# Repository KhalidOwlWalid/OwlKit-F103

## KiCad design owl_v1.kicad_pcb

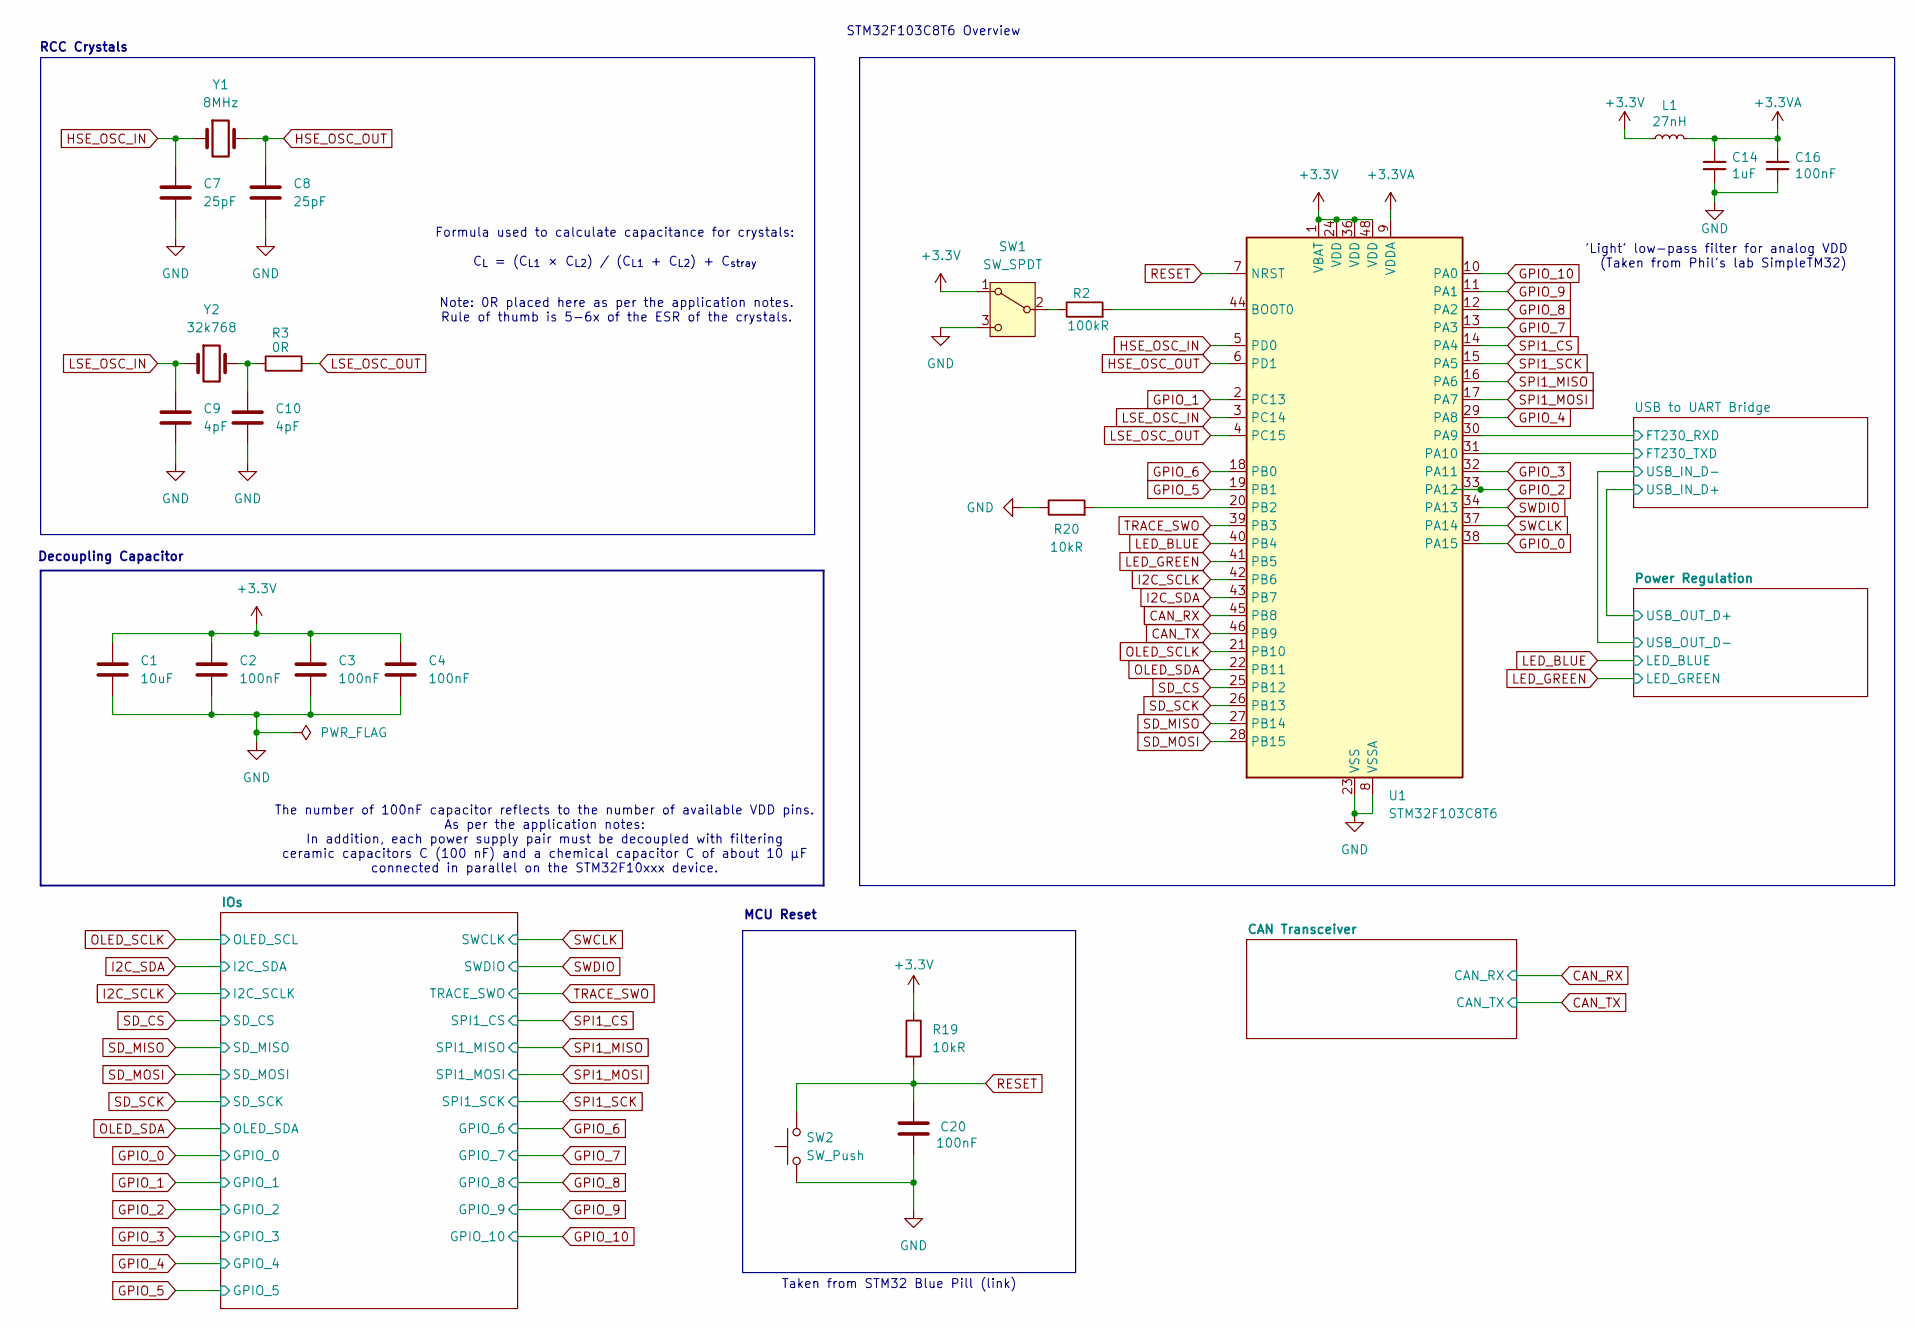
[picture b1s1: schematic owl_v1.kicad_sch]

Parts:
C1: 10uF; C_0603_1608Metric
C2, C3, C4, C20: 100nF; C_0603_1608Metric
C7, C8: 25pF; C_0603_1608Metric
C9, C10: 4pF; C_0603_1608Metric
C14: 1uF; C_0603_1608Metric; LCSC Part # C52923
C16: 100nF; C_0603_1608Metric; LCSC Part # C1525
L1: 27nH; L_0603_1608Metric; LCSC Part # C18830
R2: 100kR; R_0603_1608Metric
R3: 0R; R_0603_1608Metric
R19, R20: 10kR; R_0603_1608Metric
SW1: SW_SPDT; SW_SPDT_CK_JS102011SAQN
SW2: SW_Push; SW_PUSH_6mm
U1: STM32F103C8T6; LQFP-48_7x7mm_P0.5mm
Y1: 8MHz; Crystal_SMD_HC49-SD
Y2: 32k768; Crystal_SMD_MicroCrystal_CC8V-T1A-2Pin_2.0x1.2mm_HandSolder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

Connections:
+3.3V: C1.1, C2.1, C3.1, C4.1, L1.1, R19.1, SW1.1 (A), U1.1 (VBAT), U1.24 (VDD), U1.36 (VDD), U1.48 (VDD); also elsewhere on the board
+3.3VA: C14.1, C16.1, L1.2, U1.9 (VDDA)
/owl_v1/USB to UART Bridge/FT230_RXD: U1.30 (PA9); also elsewhere on the board
/owl_v1/USB to UART Bridge/FT230_TXD: U1.31 (PA10); also elsewhere on the board
CAN_RX: U1.45 (PB8); also elsewhere on the board
CAN_TX: U1.46 (PB9); also elsewhere on the board
GND: C1.2, C2.2, C3.2, C4.2, C7.2, C8.2, C9.2, C10.2, C14.2, C16.2, C20.1, R20.1, SW1.3 (C), SW2.1, U1.8 (VSSA), U1.23 (VSS), U1.35 (VSS), U1.47 (VSS); also elsewhere on the board
GPIO_0: U1.38 (PA15); also elsewhere on the board
GPIO_1: U1.2 (PC13); also elsewhere on the board
GPIO_2: U1.33 (PA12); also elsewhere on the board
GPIO_3: U1.32 (PA11); also elsewhere on the board
GPIO_4: U1.29 (PA8); also elsewhere on the board
GPIO_5: U1.19 (PB1); also elsewhere on the board
GPIO_6: U1.18 (PB0); also elsewhere on the board
GPIO_7: U1.13 (PA3); also elsewhere on the board
GPIO_8: U1.12 (PA2); also elsewhere on the board
GPIO_9: U1.11 (PA1); also elsewhere on the board
GPIO_10: U1.10 (PA0); also elsewhere on the board
HSE_OSC_IN: C7.1, U1.5 (PD0), Y1.1
HSE_OSC_OUT: C8.1, U1.6 (PD1), Y1.2
I2C_SCLK: U1.42 (PB6); also elsewhere on the board
I2C_SDA: U1.43 (PB7); also elsewhere on the board
LED_BLUE: U1.40 (PB4); also elsewhere on the board
LED_GREEN: U1.41 (PB5); also elsewhere on the board
LSE_OSC_IN: C9.1, U1.3 (PC14), Y2.1
LSE_OSC_OUT: R3.2, U1.4 (PC15)
unnamed: C10.1, R3.1, Y2.2
unnamed: R2.1, SW1.2 (B)
unnamed: R2.2, U1.44 (BOOT0)
unnamed: R20.2, U1.20 (PB2)
OLED_SCLK: U1.21 (PB10); also elsewhere on the board
OLED_SDA: U1.22 (PB11); also elsewhere on the board
RESET: C20.2, R19.2, SW2.2, U1.7 (NRST)
SD_CS: U1.25 (PB12); also elsewhere on the board
SD_MISO: U1.27 (PB14); also elsewhere on the board
SD_MOSI: U1.28 (PB15); also elsewhere on the board
SD_SCK: U1.26 (PB13); also elsewhere on the board
SPI1_CS: U1.14 (PA4); also elsewhere on the board
SPI1_MISO: U1.16 (PA6); also elsewhere on the board
SPI1_MOSI: U1.17 (PA7); also elsewhere on the board
SPI1_SCK: U1.15 (PA5); also elsewhere on the board
SWCLK: U1.37 (PA14); also elsewhere on the board
SWDIO: U1.34 (PA13); also elsewhere on the board
TRACE_SWO: U1.39 (PB3); also elsewhere on the board

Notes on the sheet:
MCU Reset
Formula used to calculate capacitance for crystals: C_{L} = (C_{L1} × C_{L2}) / (C_{L1} + C_{L2}) + C_{stray}
RCC Crystals
STM32F103C8T6 Overview
The number of 100nF capacitor reflects to the number of available VDD pins. As per the application notes: In addition, each power supply pair must be decoupled with filtering ceramic capacitors C (100 nF) and a chemical capacitor C of about 10 μF connected in parallel on the STM32F10xxx device.
Decoupling Capacitor
Taken from STM32 Blue Pill (link)
Note: 0R placed here as per the application notes. Rule of thumb is 5-6x of the ESR of the crystals.
'Light' low-pass filter for analog VDD (Taken from Phil's lab SimpleTM32)

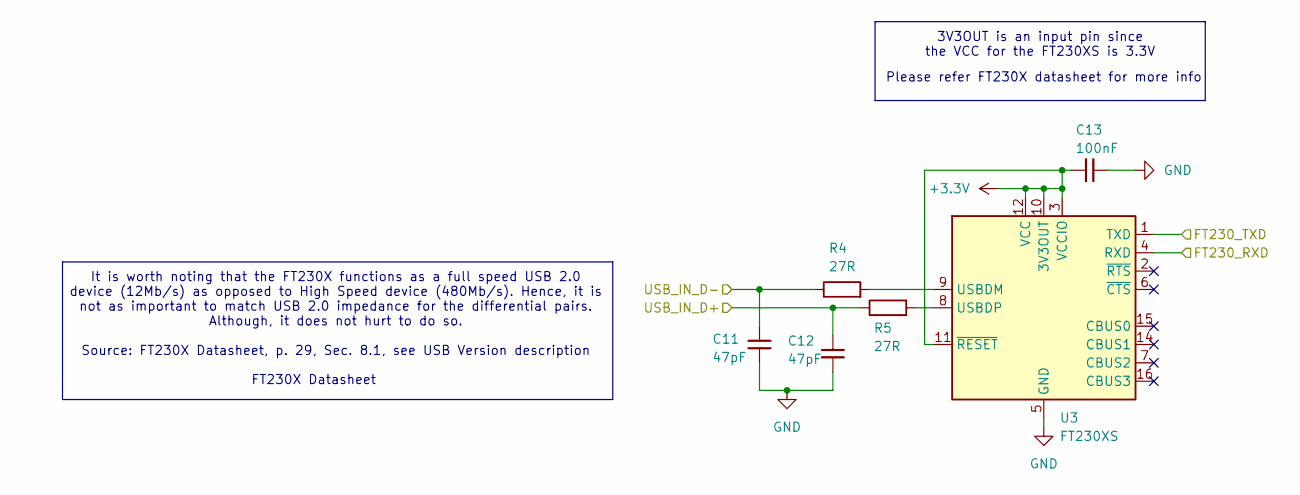
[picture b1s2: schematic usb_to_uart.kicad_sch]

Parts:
C11, C12: 47pF; C_0603_1608Metric
C13: 100nF; C_0603_1608Metric
R4, R5: 27R; R_0603_1608Metric
U3: FT230XS; SSOP-16_3.9x4.9mm_P0.635mm

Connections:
+3.3V: C13.2, U3.3 (VCCIO), U3.10 (3V3OUT), U3.11 (~RESET), U3.12 (VCC); also elsewhere on the board
/owl_v1/Power Regulation/USB_OUT_D+: C12.1, R5.1; also elsewhere on the board
/owl_v1/Power Regulation/USB_OUT_D-: C11.1, R4.1; also elsewhere on the board
/owl_v1/USB to UART Bridge/FT230_RXD: U3.4 (RXD); also elsewhere on the board
/owl_v1/USB to UART Bridge/FT230_TXD: U3.1 (TXD); also elsewhere on the board
GND: C11.2, C12.2, C13.1, U3.5 (GND), U3.13 (GND); also elsewhere on the board
unnamed: R4.2, U3.9 (USBDM)
unnamed: R5.2, U3.8 (USBDP)

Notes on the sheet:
Please refer FT230X datasheet for more info
3V3OUT is an input pin since the VCC for the FT230XS is 3.3V
FT230X Datasheet
It is worth noting that the FT230X functions as a full speed USB 2.0 device (12Mb/s) as opposed to High Speed device (480Mb/s). Hence, it is not as important to match USB 2.0 impedance for the differential pairs. Although, it does not hurt to do so. Source: FT230X Datasheet, p. 29, Sec. 8.1, see US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

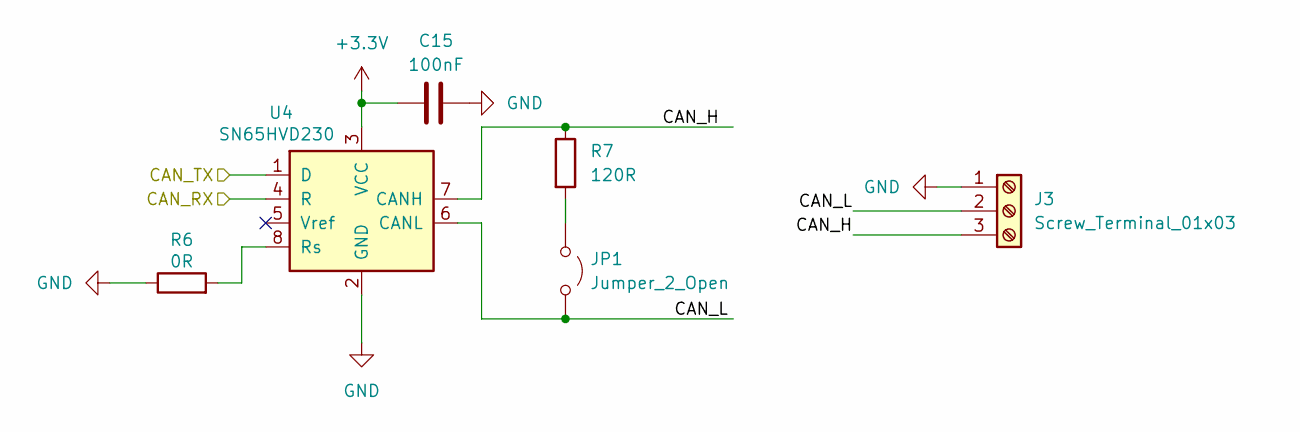
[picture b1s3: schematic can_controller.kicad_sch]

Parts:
C15: 100nF; C_0603_1608Metric
J3: Screw_Terminal_01x03; TerminalBlock_Phoenix_PT-1,5-3-3.5-H_1x03_P3.50mm_Horizontal
JP1: Jumper_2_Open; PinHeader_1x02_P2.54mm_Vertical
R6: 0R; R_0603_1608Metric
R7: 120R; R_0603_1608Metric
U4: SN65HVD230; SOIC-8_3.9x4.9mm_P1.27mm

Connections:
+3.3V: C15.1, U4.3 (VCC); also elsewhere on the board
/owl_v1/CAN Transceiver/CAN_H: J3.3, R7.1, U4.7 (CANH)
/owl_v1/CAN Transceiver/CAN_L: J3.2, JP1.2 (B), U4.6 (CANL)
CAN_RX: U4.4 (R); also elsewhere on the board
CAN_TX: U4.1 (D); also elsewhere on the board
GND: C15.2, J3.1, R6.1, U4.2 (GND); also elsewhere on the board
unnamed: JP1.1 (A), R7.2
unnamed: R6.2, U4.8 (Rs)

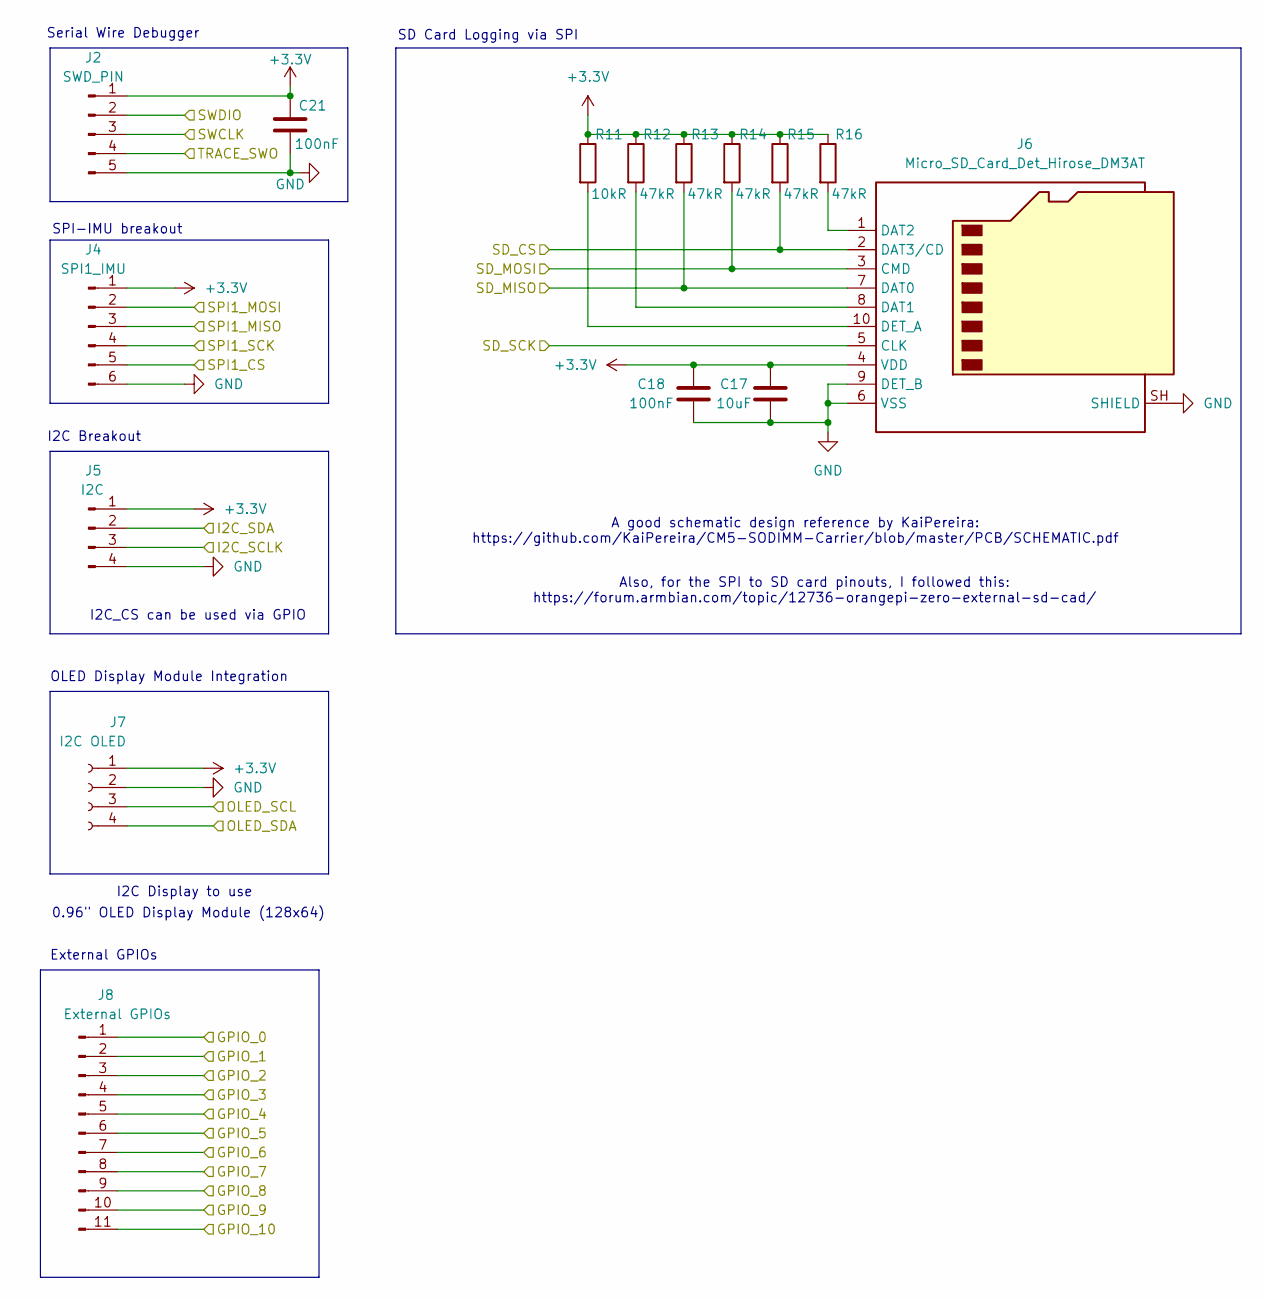
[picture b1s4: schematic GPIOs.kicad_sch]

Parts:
C17: 10uF; C_0603_1608Metric
C18, C21: 100nF; C_0603_1608Metric
J2: SWD_PIN; PinHeader_1x05_P2.54mm_Vertical
J4: SPI1_IMU; PinHeader_1x06_P2.54mm_Vertical
J5: I2C; PinHeader_1x04_P2.54mm_Vertical
J6: Micro_SD_Card_Det_Hirose_DM3AT; microSD_HC_Hirose_DM3AT-SF-PEJM5
J7: I2C OLED; PinSocket_1x04_P2.54mm_Vertical
J8: External GPIOs; PinHeader_1x11_P2.54mm_Vertical
R11: 10kR; R_0603_1608Metric
R12, R13, R14, R15, R16: 47kR; R_0603_1608Metric

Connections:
+3.3V: C17.1, C18.1, C21.1, J2.1, J4.1, J5.1, J6.4 (VDD), J7.1, R11.1, R12.1, R13.1, R14.1, R15.1, R16.1; also elsewhere on the board
GND: C17.2, C18.2, C21.2, J2.5, J4.6, J5.4, J6.6 (VSS), J6.9 (DET_B), J6.SH (SHIELD), J7.2; also elsewhere on the board
GPIO_0: J8.1; also elsewhere on the board
GPIO_1: J8.2; also elsewhere on the board
GPIO_2: J8.3; also elsewhere on the board
GPIO_3: J8.4; also elsewhere on the board
GPIO_4: J8.5; also elsewhere on the board
GPIO_5: J8.6; also elsewhere on the board
GPIO_6: J8.7; also elsewhere on the board
GPIO_7: J8.8; also elsewhere on the board
GPIO_8: J8.9; also elsewhere on the board
GPIO_9: J8.10; also elsewhere on the board
GPIO_10: J8.11; also elsewhere on the board
I2C_SCLK: J5.3; also elsewhere on the board
I2C_SDA: J5.2; also elsewhere on the board
unnamed: J6.8 (DAT1), R12.2
unnamed: J6.1 (DAT2), R16.2
unnamed: J6.10 (DET_A), R11.2
OLED_SCLK: J7.3; also elsewhere on the board
OLED_SDA: J7.4; also elsewhere on the board
SD_CS: J6.2 (DAT3/CD), R15.2; also elsewhere on the board
SD_MISO: J6.7 (DAT0), R13.2; also elsewhere on the board
SD_MOSI: J6.3 (CMD), R14.2; also elsewhere on the board
SD_SCK: J6.5 (CLK); also elsewhere on the board
SPI1_CS: J4.5; also elsewhere on the board
SPI1_MISO: J4.3; also elsewhere on the board
SPI1_MOSI: J4.2; also elsewhere on the board
SPI1_SCK: J4.4; also elsewhere on the board
SWCLK: J2.3; also elsewhere on the board
SWDIO: J2.2; also elsewhere on the board
TRACE_SWO: J2.4; also elsewhere on the board

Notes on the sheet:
Also, for the SPI to SD card pinouts, I followed this: https://forum.armbian.com/topic/12736-orangepi-zero-external-sd-cad/
Serial Wire Debugger
External GPIOs
SD Card Logging via SPI
0.96" OLED Display Module (128x64)
I2C Breakout
I2C_CS can be used via GPIO
SPI-IMU breakout
OLED Display Module Integration
I2C Display to use
A good schematic design reference by KaiPereira: https://github.com/KaiPereira/CM5-SODIMM-Carrier/blob/master/PCB/SCHEMATIC.pdf

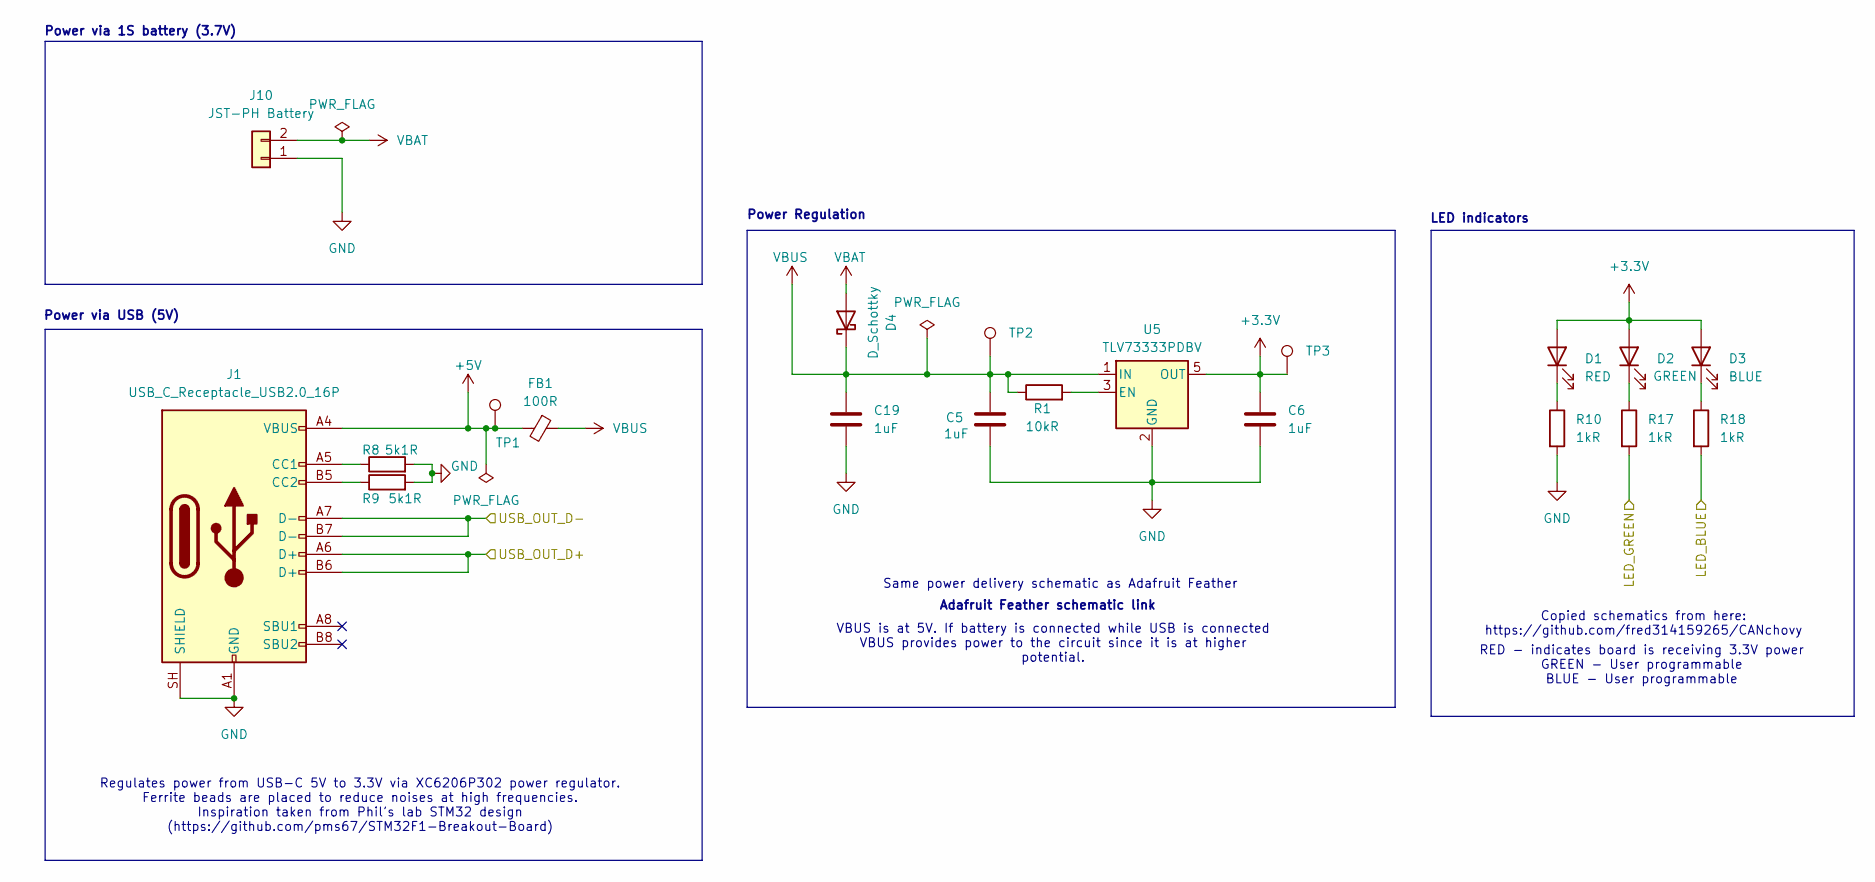
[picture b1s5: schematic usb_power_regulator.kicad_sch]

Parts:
C5, C6, C19: 1uF; C_0603_1608Metric
D1: RED; LED_0603_1608Metric
D2: GREEN; LED_0603_1608Metric
D3: BLUE; LED_0603_1608Metric
D4: D_Schottky; D_0603_1608Metric
FB1: 100R; L_0603_1608Metric
J1: USB_C_Receptacle_USB2.0_16P; USB_C_Receptacle_GCT_USB4105-xx-A_16P_TopMnt_Horizontal
J10: JST-PH Battery; JST_PH_S2B-PH-K_1x02_P2.00mm_Horizontal
R1: 10kR; R_0603_1608Metric
R8, R9: 5k1R; R_0603_1608Metric
R10, R17, R18: 1kR; R_0603_1608Metric
TP1, TP2, TP3: TestPoint_Pad_D1.5mm
U5: TLV73333PDBV; SOT-23-5

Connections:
+3.3V: C6.1, D1.2 (A), D2.2 (A), D3.2 (A), TP3.1 (1_1), U5.5 (OUT); also elsewhere on the board
+5V: FB1.2, J1.A4 (VBUS), J1.A9 (VBUS), J1.B4 (VBUS), J1.B9 (VBUS), TP1.1 (1_1)
/owl_v1/Power Regulation/USB_OUT_D+: J1.A6 (D+), J1.B6 (D+); also elsewhere on the board
/owl_v1/Power Regulation/USB_OUT_D-: J1.A7 (D-), J1.B7 (D-); also elsewhere on the board
GND: C5.2, C6.2, C19.2, J1.A1 (GND), J1.A12 (GND), J1.B1 (GND), J1.B12 (GND), J1.SH (SHIELD), J10.1, R8.2, R9.2, R10.2, U5.2 (GND); also elsewhere on the board
LED_BLUE: R18.2; also elsewhere on the board
LED_GREEN: R17.2; also elsewhere on the board
unnamed: D1.1 (K), R10.1
unnamed: D2.1 (K), R17.1
unnamed: D3.1 (K), R18.1
unnamed: J1.A5 (CC1), R8.1
unnamed: J1.B5 (CC2), R9.1
unnamed: R1.2, U5.3 (EN)
VBAT: D4.2 (A), J10.2
VBUS: C5.1, C19.1, D4.1 (K), FB1.1, R1.1, TP2.1 (1_1), U5.1 (IN)

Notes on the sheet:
VBUS is at 5V. If battery is connected while USB is connected VBUS provides power to the circuit since it is at higher potential.
Same power delivery schematic as Adafruit Feather
LED indicators
RED - indicates board is receiving 3.3V power GREEN - User programmable BLUE - User programmable
Regulates power from USB-C 5V to 3.3V via XC6206P302 power regulator. Ferrite beads are placed to reduce noises at high frequencies. Inspiration taken from Phil's lab STM32 design (https://github.com/pms67/STM32F1-Breakout-Board)
Copied schematics from here: https://github.com/fred314159265/CANchovy
Power via USB (5V)
Power Regulation
Power via 1S battery (3.7V)
Adafruit Feather schematic link

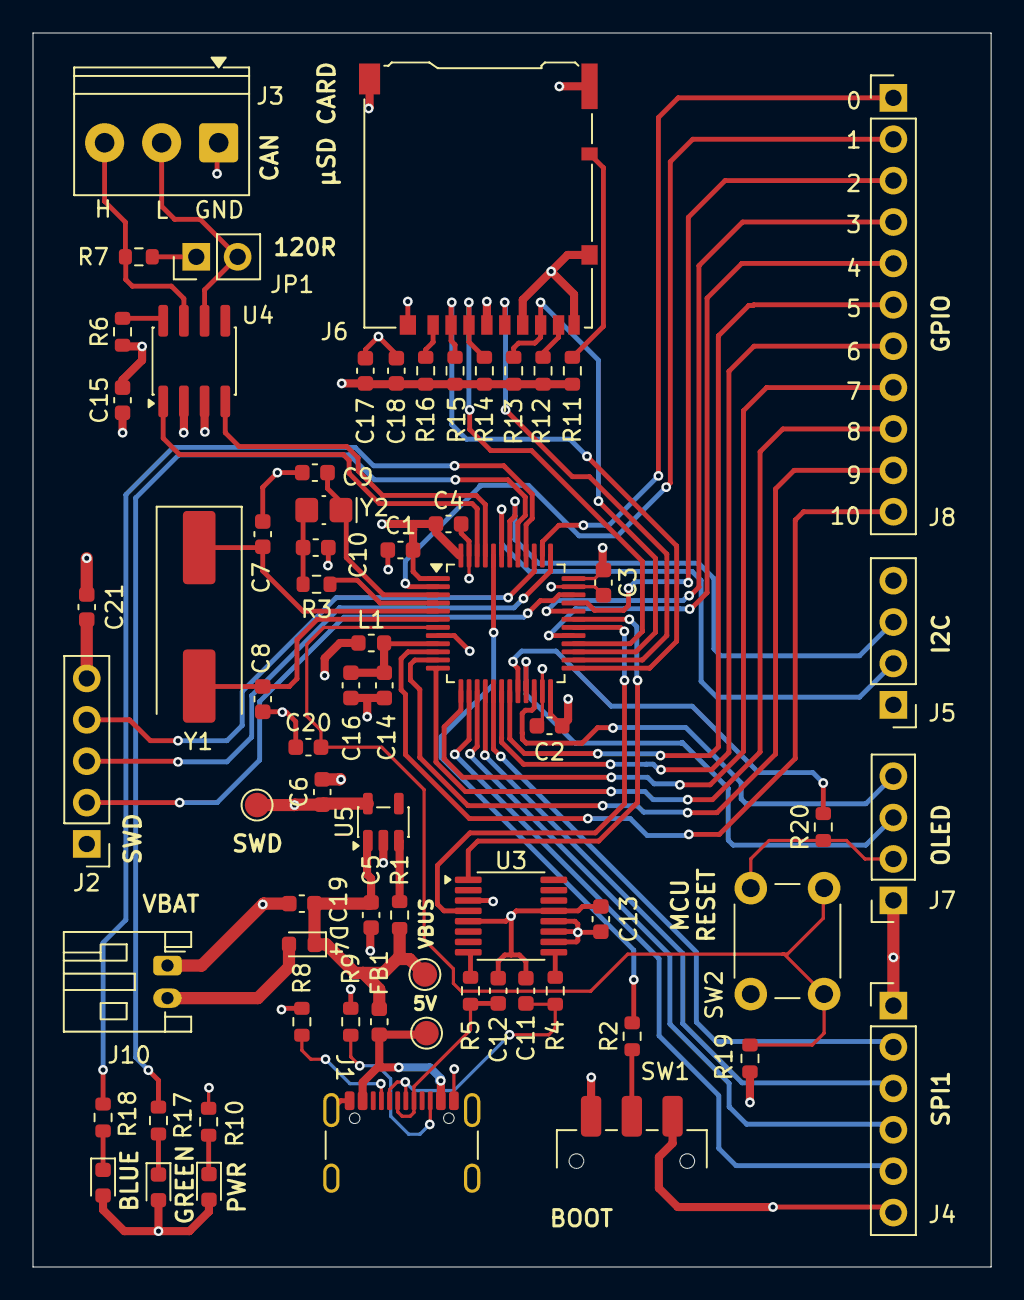
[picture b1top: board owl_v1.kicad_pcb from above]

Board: 4 copper layers, 58.8 x 75.7 mm, 69 parts (1 on the bottom side), 64 nets.

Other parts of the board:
Owl Kit v0.1: LOGO
